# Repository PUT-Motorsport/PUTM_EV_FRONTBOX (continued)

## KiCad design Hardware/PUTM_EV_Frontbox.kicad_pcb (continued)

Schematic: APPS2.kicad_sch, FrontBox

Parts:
C50, C51, C52: 100n; C_0603_1608Metric_Pad1.08x0.95mm_HandSolder; Mouser Part Number .
C53: 10n; C_0603_1608Metric_Pad1.08x0.95mm_HandSolder; Mouser Part Number .; not fitted
R23, R27, R28, R29: 1K; R_0603_1608Metric_Pad0.98x0.95mm_HandSolder; Mouser Part Number .
R24: 100k; R_0603_1608Metric_Pad0.98x0.95mm_HandSolder; Mouser Part Number .
R25: 0R; R_0603_1608Metric_Pad0.98x0.95mm_HandSolder; Mouser Part Number .
R26: 325R; R_0603_1608Metric_Pad0.98x0.95mm_HandSolder; Mouser Part Number .
TP7: APPS_P; TestPoint_THTPad_D1.0mm_Drill0.5mm
TP8: APPS_OUT; TestPoint_THTPad_D1.0mm_Drill0.5mm
TP9: APPS_N; TestPoint_THTPad_D1.0mm_Drill0.5mm
U10: MCP6N11-001E/SN; SOIC-8_3.9x4.9mm_P1.27mm; Mouser Part Number 579-MCP6N11-001E/SN

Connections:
/APPS2_SHIFTED_3V3: R23.1; also elsewhere on the board
/APPS2_SHIFTED_GND: R26.2; also elsewhere on the board
/APPS2_SUPPLY: C50.1, C51.1, R23.2, R25.2, U10.7 (V+); also elsewhere on the board
/APPS_POT_2: R24.1, TP7.1, U10.3 (+); also elsewhere on the board
/APPS_SIG2: C52.1, R27.2, TP8.1; also elsewhere on the board
/DAC2_REF: C53.1, TP9.1, U10.2 (-); also elsewhere on the board
GND: C50.2, C51.2, C52.2, C53.2, R24.2, R26.1, R29.1, U10.4 (V-), U10.5 (RF); also elsewhere on the board
unnamed: R27.1, R28.2, U10.6
unnamed: R25.1, U10.8 (EN)
unnamed: R28.1, R29.2, U10.1 (FG)

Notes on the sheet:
3V3_POT2
Instrumentation Amplifier
Currently 1,566V - should be smaller than POT voltage
G = 2
f_{c} ≈ 1591
GND
Low-pass Filter
7K5
325R

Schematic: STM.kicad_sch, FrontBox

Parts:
C19: 10u; C_0805_2012Metric_Pad1.18x1.45mm_HandSolder; Mouser Part Number .
C20, C21, C22, C23, C24, C25, C26: 100nF; C_0603_1608Metric_Pad1.08x0.95mm_HandSolder; Mouser Part Number .
C27: 100n; C_0603_1608Metric; Mouser Part Number .
D11, D12, D13, D14: LED; LED_0603_1608Metric_Pad1.05x0.95mm_HandSolder; Mouser Part Number .
FB10: 2K@100MHz; L_0805_2012Metric_Pad1.05x1.20mm_HandSolder; Mouser Part Number 623-2508052027Y1
JP2: Jumper_2_Small_Bridged; SolderJumper-2_P1.3mm_Open_TrianglePad1.0x1.5mm; Mouser Part Number .
R6: 1k; R_0603_1608Metric; Mouser Part Number .
R7, R9: 10k; R_0603_1608Metric; Mouser Part Number .
R8: 10k; R_0603_1608Metric; Mouser Part Number .; not fitted
R10, R11, R12, R13: 1K; R_0603_1608Metric_Pad0.98x0.95mm_HandSolder; Mouser Part Number .
TP3: TestPoint_Small; TestPoint_THTPad_D1.0mm_Drill0.5mm
U5: LM4040C33FTA; SOT-23; Mouser Part Number 621-LM4040C33FTA
U6: STM32G484RETx; LQFP-64_10x10mm_P0.5mm; Mouser Part Number .

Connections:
+3.3V: C19.1, C20.1, C21.1, C22.1, C23.1, C24.1, D11.2 (A), D12.2 (A), D13.2 (A), D14.2 (A), FB10.1, R7.1, R8.1, U6.1 (VBAT), U6.16 (VDD), U6.32 (VDD), U6.48 (VDD), U6.64 (VDD); also elsewhere on the board
+3.3VA: C25.1, FB10.2, U6.29 (VDDA); also elsewhere on the board
+5V: R6.1; also elsewhere on the board
/APPS_SIG1: U6.18 (ADC2_IN17); also elsewhere on the board
/APPS_SIG2: U6.17 (ADC1_IN4); also elsewhere on the board
/BRAKE_PRESSURE_FRONT_OUT: U6.22 (ADC2_IN5); also elsewhere on the board
/BRAKE_PRESSURE_REAR_OUT: U6.21 (ADC2_IN4); also elsewhere on the board
/CAN bus/CAN1_RX: U6.45 (FDCAN1_RX); also elsewhere on the board
/CAN bus/CAN1_TX: U6.46 (FDCAN1_TX); also elsewhere on the board
/CAN bus/CAN2_RX: U6.34 (FDCAN2_RX); also elsewhere on the board
/CAN bus/CAN2_TX: U6.35 (FDCAN2_TX); also elsewhere on the board
/CAN bus/STBY_CAN_1: U6.3 (PC14); also elsewhere on the board
/CAN bus/STBY_CAN_2: U6.4 (PC15); also elsewhere on the board
/Connector/NRST: C27.1, JP2.2 (B), R7.2, U6.7 (PG10); also elsewhere on the board
/Connector/SWCLK: U6.50 (SYS_JTCK-SWCLK); also elsewhere on the board
/Connector/SWDIO: U6.49 (SYS_JTMS-SWDIO); also elsewhere on the board
/Connector/SWO: U6.56 (SYS_JTDO-SWO); also elsewhere on the board
/Connector/UART_RX: U6.44 (USART1_RX); also elsewhere on the board
/Connector/UART_RX_PROG: U6.30 (LPUART1_RX); also elsewhere on the board
/Connector/UART_TX: U6.43 (USART1_TX); also elsewhere on the board
/Connector/UART_TX_PROG: U6.9 (LPUART1_TX); also elsewhere on the board
/DAC1_REF: U6.20 (DAC2_OUT1); also elsewhere on the board
/DAC2_REF: U6.19 (DAC1_OUT2); also elsewhere on the board
/HSE_IN: U6.5 (RCC_OSC_IN); also elsewhere on the board
/MCU/BOOT: R8.2, R9.1, U6.61 (PB8)
/MCU/BSPD_S: U6.62 (PB9); also elsewhere on the board
/MCU/DEBUG_LED1: R10.2, U6.39 (PC7)
/MCU/DEBUG_LED2: R11.2, U6.38 (PC6)
/MCU/DEBUG_LED3: R12.2, U6.37 (PB15)
/MCU/DEBUG_LED4: R13.2, U6.36 (PB14)
/MCU/DRIVER_KILL_S: U6.54 (PC12); also elsewhere on the board
/MCU/EBS_S: U6.52 (PC10); also elsewhere on the board
/MCU/INERTIA_S: U6.51 (PA15); also elsewhere on the board
/MCU/LEFT_KILL_S: U6.53 (PC11); also elsewhere on the board
/MCU/LEFT_WHEEL_S: U6.57 (PB4); also elsewhere on the board
/MCU/OVERTRAVEL_S: U6.59 (PB6); also elsewhere on the board
/MCU/RIGHT_KILL_S: U6.60 (PB7); also elsewhere on the board
/MCU/RIGHT_WHEEL_S: U6.58 (PB5); also elsewhere on the board
/MCU/Tens1: U6.12 (ADC1_IN1); also elsewhere on the board
/MCU/Tens2: U6.13 (ADC1_IN2); also elsewhere on the board
/MCU/VREF: C26.1, R6.2, TP3.1, U5.1 (K), U6.28 (VREF+)
/MCU/XIAO_GPIO: U6.42 (PA8); also elsewhere on the board
GND: C19.2, C20.2, C21.2, C22.2, C23.2, C24.2, C25.2, C26.2, C27.2, JP2.1 (A), R9.2, U5.2 (A), U6.15 (VSS), U6.27 (VSSA), U6.31 (VSS), U6.47 (VSS), U6.63 (VSS); also elsewhere on the board
unnamed: D11.1 (K), R10.1
unnamed: D12.1 (K), R11.1
unnamed: D13.1 (K), R12.1
unnamed: D14.1 (K), R13.1

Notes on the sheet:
MCU
Decoupling capacitors
Debug LEDs

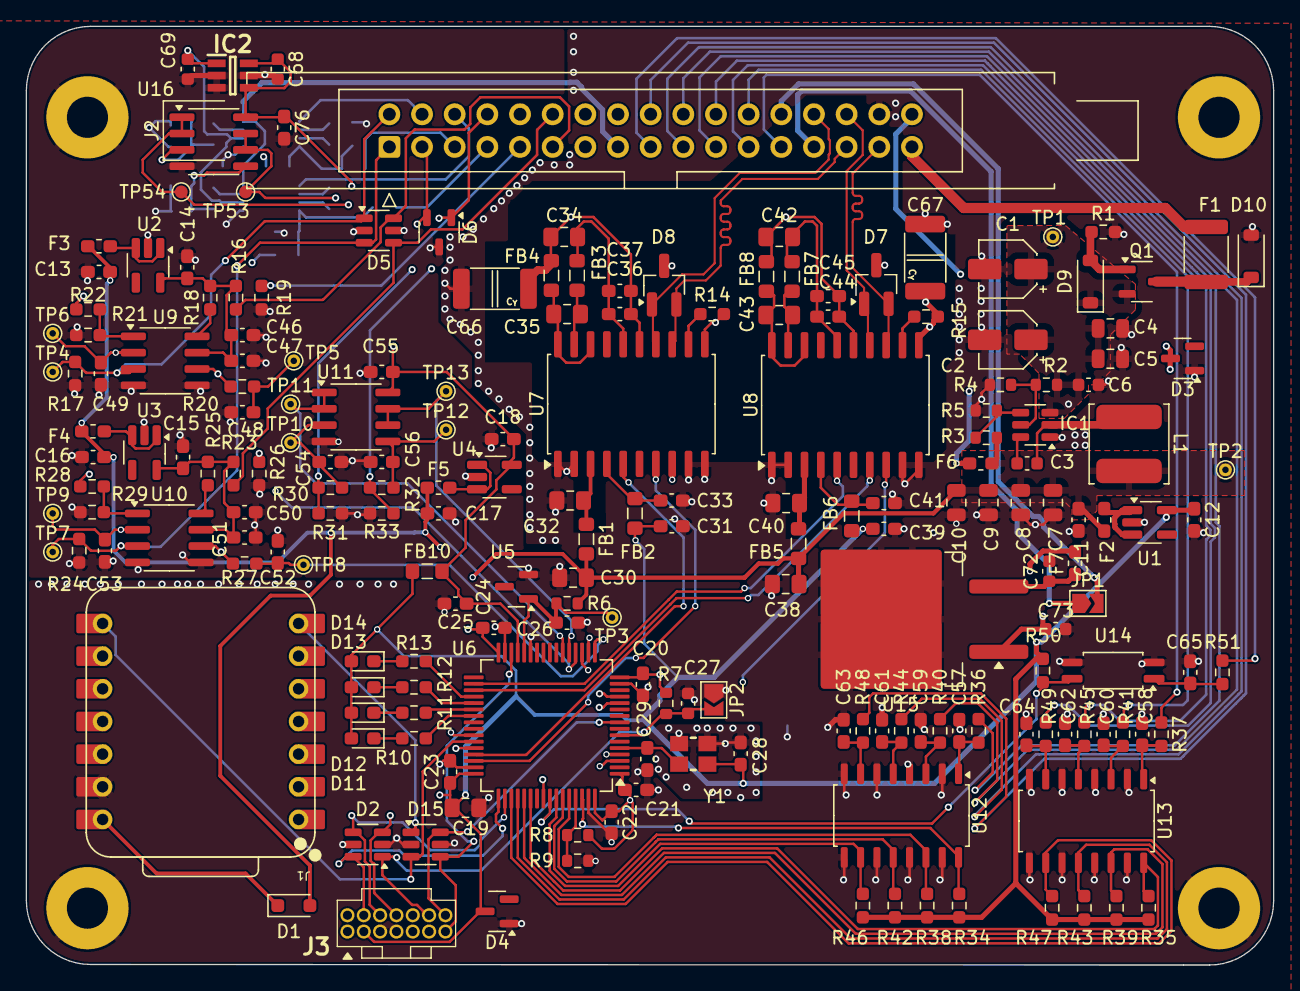
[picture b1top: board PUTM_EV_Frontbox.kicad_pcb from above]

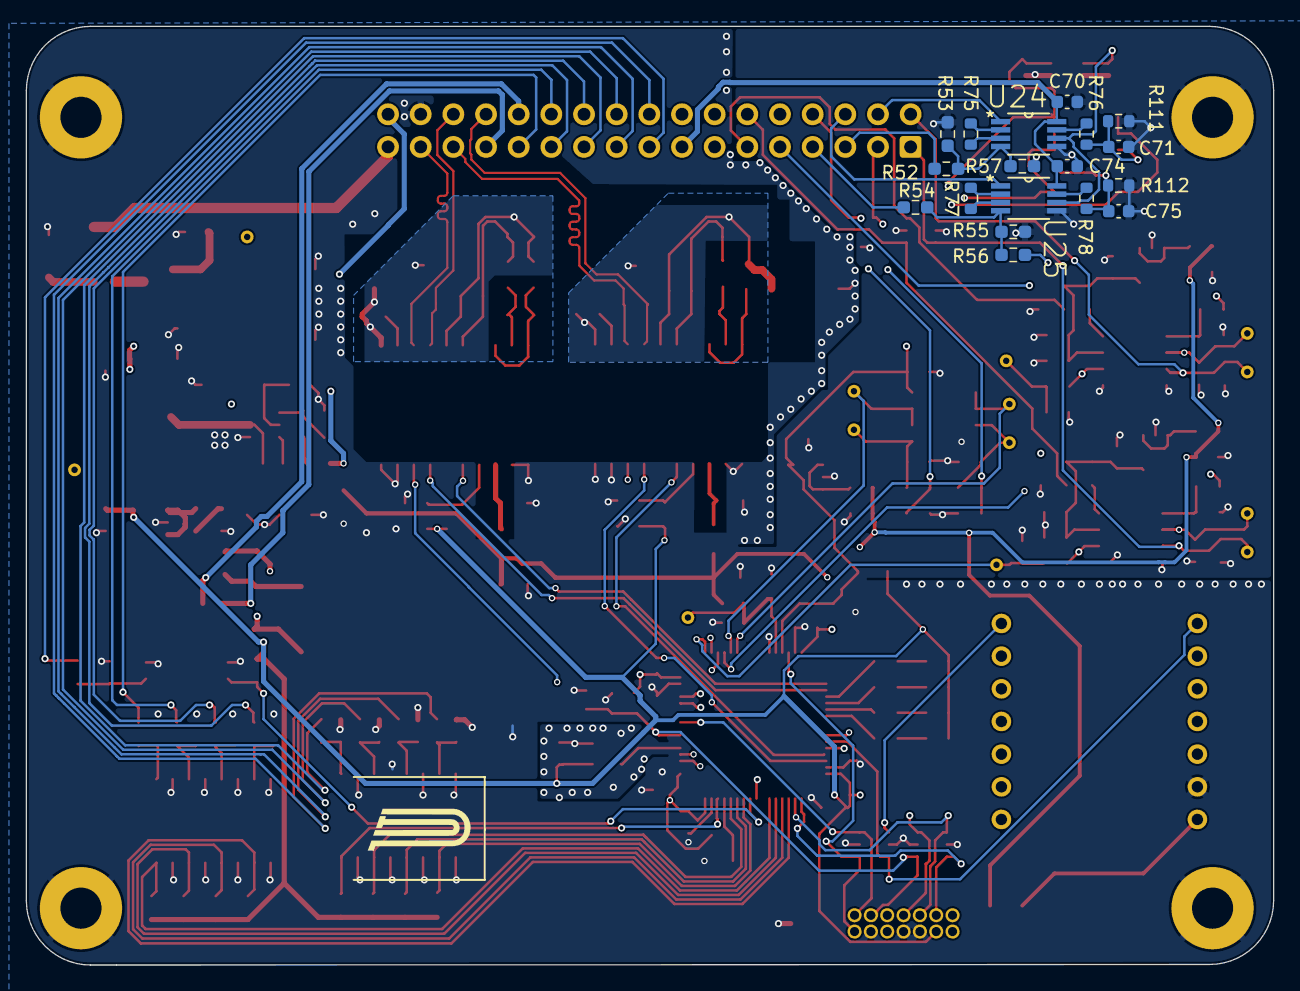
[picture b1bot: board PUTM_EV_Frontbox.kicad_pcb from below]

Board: 4 copper layers, 97.0 x 73.0 mm, 213 parts (18 on the bottom side), 134 nets.

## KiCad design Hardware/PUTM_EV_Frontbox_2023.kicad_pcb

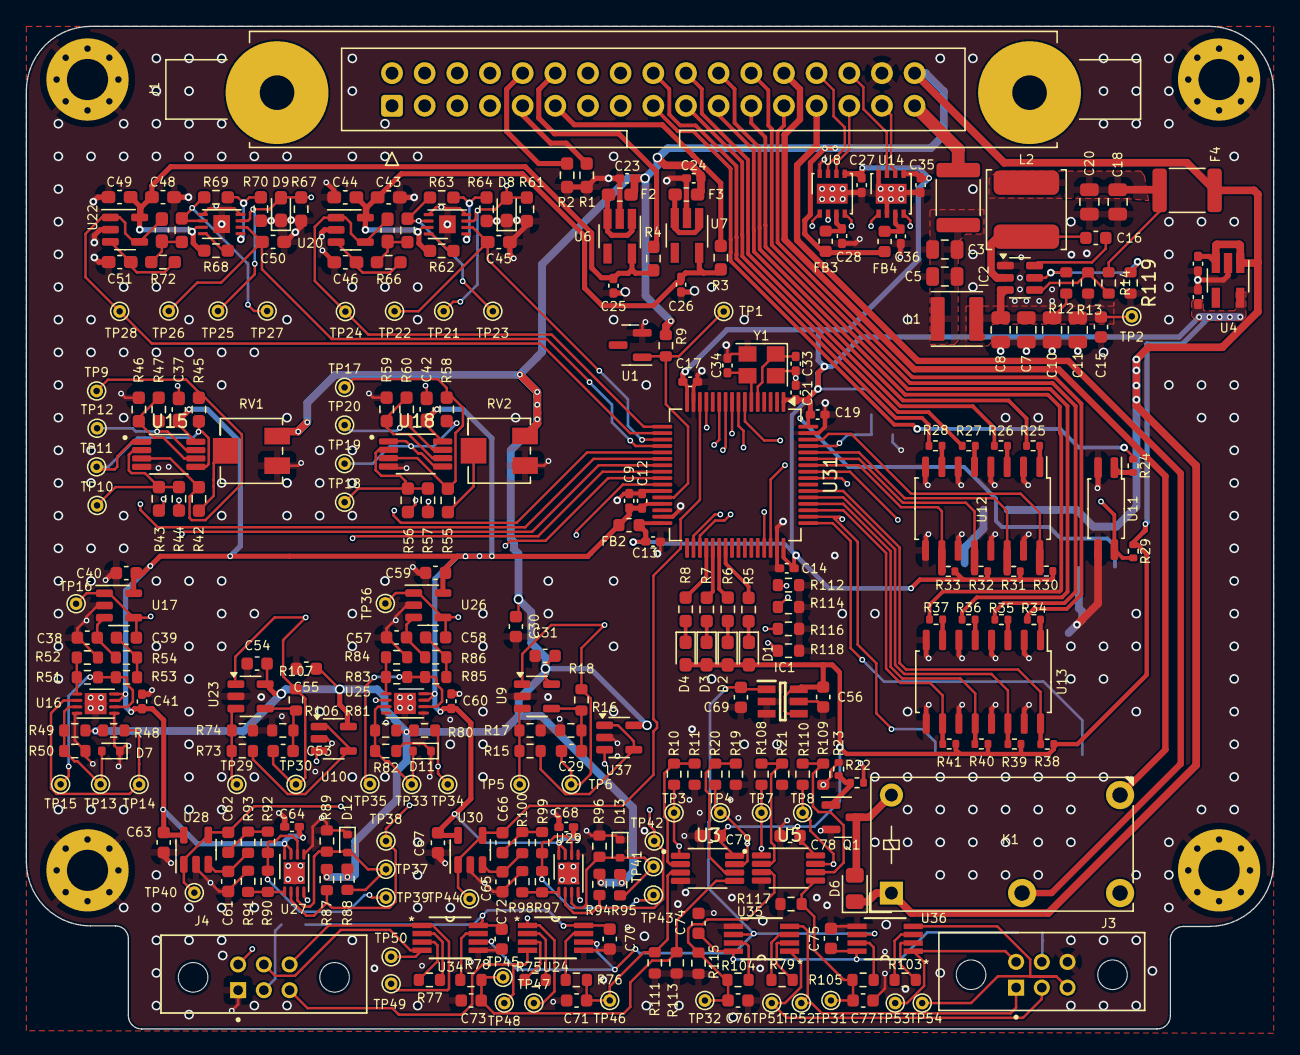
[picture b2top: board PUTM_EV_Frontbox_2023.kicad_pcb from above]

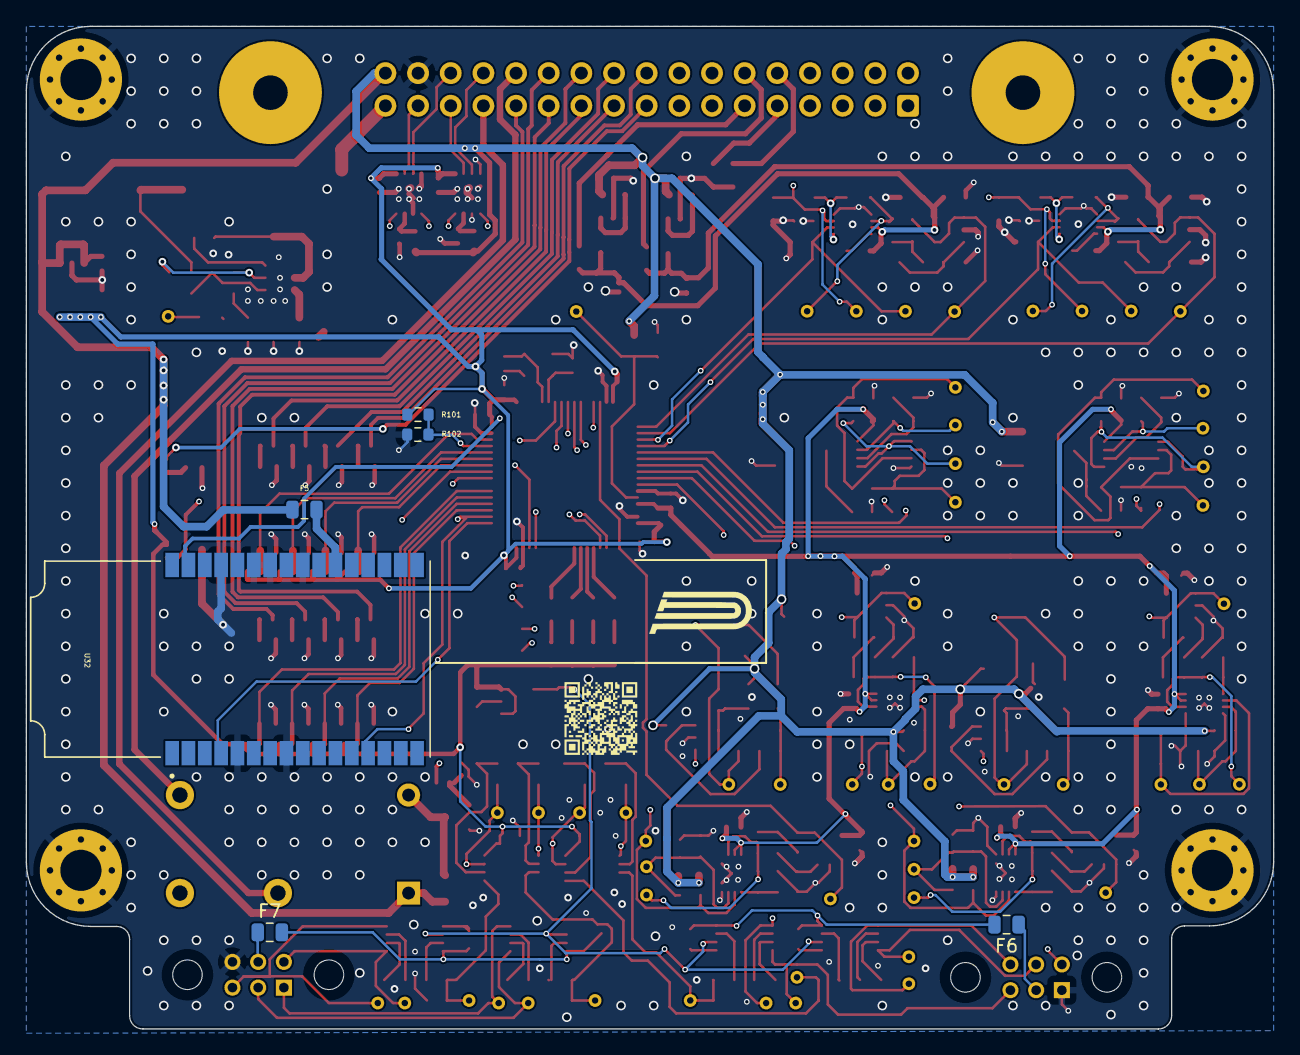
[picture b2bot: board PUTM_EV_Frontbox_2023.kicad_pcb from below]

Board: 4 copper layers, 97.0 x 78.0 mm, 320 parts (6 on the bottom side), 183 nets.

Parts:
C3, C5: 2u2; C_0805_2012Metric
C4, C6, C9, C23, C24, C25, C26: 1uF; C_0402_1005Metric_Pad0.74x0.62mm_HandSolder
C7, C8: 4u7; C_0805_2012Metric
C10, C11, C18, C20: 22uF; C_0805_2012Metric
C12, C13, C14, C17, C19, C21, C27, C28, C35, C36: 100nF; C_0402_1005Metric_Pad0.74x0.62mm_HandSolder
C15, C16: 100nF; C_0603_1608Metric
C29, C53: 10n; C_0603_1608Metric
C30, C31, C38, C39, C40, C54, C55, C57, C58, C59, C61, C62, C63, C65, C66, C67, C70, C72, C74, C75, C78, C79: 100n; C_0603_1608Metric
C33, C34: 10pF; C_0402_1005Metric_Pad0.74x0.62mm_HandSolder
C37, C42, C43, C44, C46, C47, C48, C49, C51, C52: 100n; C_0603_1608Metric_Pad1.08x0.95mm_HandSolder
C41, C60, C64, C68: 100n; C_0402_1005Metric_Pad0.74x0.62mm_HandSolder
C45, C50: 10n; C_0603_1608Metric_Pad1.08x0.95mm_HandSolder
C56, C71, C73, C76, C77: 1u; C_0603_1608Metric
C69: 1n; C_0603_1608Metric
D1, D2, D3, D4: LED; LED_0603_1608Metric_Pad1.05x0.95mm_HandSolder
D6: D_Small; D_0805_2012Metric_Pad1.15x1.40mm_HandSolder
D7, D11, D12, D13: 5V; D_SOD-523
D8, D9: 24V; D_0603_1608Metric_Pad1.05x0.95mm_HandSolder
F1, F4: 1.5A; Fuse_1812_4532Metric
F2, F3: 300mA; Fuse_0603_1608Metric_Pad1.05x0.95mm_HandSolder
F5: Fuse_Small; Fuse_0805_2012Metric
F6, F7: 0.5A; Fuse_0805_2012Metric
FB2: 1000Ω@100MHz; L_0603_1608Metric
FB3, FB4: 60R@100MHz; L_0603_1608Metric
H1, H2, H3, H4: MountingHole_Pad; MountingHole_3.2mm_M3_Pad_Via
IC1: MCP1501T-18E_CHY; SOT95P270X145-6N
IC2: TPS54202HDDCR; SOT-23-6
J1: Conn_02x16_Counter_Clockwise; IDC-Header_2x17-1MP_P2.54mm_Latch6.5mm_Vertical
J3, J4: M80-5100622; M80-5100622_HARWIN_M80-5100622
K1: FINDER-32.21-x000; Relay_SPDT_Finder_32.21-x000
L1: 1u5; L_Abracon_ASPI-4030S
L2: 68uH/1.4A; L_TDK_VLS6045EX_VLS6045AF
Q1: NX7002AK; SOT-23
R1, R2, R3, R4: 220R; R_0603_1608Metric_Pad0.98x0.95mm_HandSolder
R5, R6, R7, R8, R42, R44, R55, R57: 100R; R_0603_1608Metric_Pad0.98x0.95mm_HandSolder
R9, R75, R77, R79, R103: 1k; R_0603_1608Metric
R10, R11, R19, R20, R21, R108, R109, R110: 0R; R_0603_1608Metric
R12: 510k; R_0603_1608Metric
R13: 13.3k; R_0603_1608Metric
R14: 100k; R_0603_1608Metric
R15, R16, R73, R106: 20k; R_0603_1608Metric
R17, R18, R74, R101, R102, R107: 10k; R_0603_1608Metric
R22: 200R; R_0402_1005Metric
R23, R29, R30, R31, R32, R33, R38, R39, R40, R41: 10k; R_0402_1005Metric
R24, R25, R26, R27, R28, R34, R35, R36, R37: 2k; R_0402_1005Metric
R43, R45, R47, R56, R58, R60, R62, R68: 0R; R_0603_1608Metric_Pad0.98x0.95mm_HandSolder
R46, R59: 3k3; R_0603_1608Metric_Pad0.98x0.95mm_HandSolder
R48, R49, R80, R81, R87, R88, R94, R95: 50k; R_0603_1608Metric
R50, R82, R89, R96: 5k; R_0603_1608Metric
R51, R52, R83, R84, R90, R91, R97, R98: TBD; R_0603_1608Metric
R53, R54, R85, R86, R92, R93, R99, R100: 3k3; R_0603_1608Metric
R61, R67: 100k; R_0603_1608Metric_Pad0.98x0.95mm_HandSolder
R63, R65, R66, R69, R71, R72: 4k7; R_0603_1608Metric_Pad0.98x0.95mm_HandSolder
R64, R70: 1k; R_0603_1608Metric_Pad0.98x0.95mm_HandSolder
R76, R78, R104, R105: 330; R_0603_1608Metric
R111, R112, R113, R114, R115, R116, R117, R118: 100K; R_0603_1608Metric
R119: 43k; R_0603_1608Metric
RV1, RV2: 2k; Potentiometer_Bourns_3214J_Horizontal
TP1, TP2, TP5, TP6, TP13, TP14, TP15, TP16, TP29, TP30, TP33, TP34, TP35, TP36, TP37, TP38, TP39, TP40, TP41, TP42, TP43, TP44: TestPoint_Small; TestPoint_THTPad_D1.0mm_Drill0.5mm
TP3, TP4, TP7, TP8, TP9, TP17, TP31, TP32, TP45, TP46, TP47, TP48, TP49, TP50, TP51, TP52, TP53, TP54: BR_N; TestPoint_THTPad_D1.0mm_Drill0.5mm
TP10, TP18: BR_P; TestPoint_THTPad_D1.0mm_Drill0.5mm
TP11, TP19: BR_MID; TestPoint_THTPad_D1.0mm_Drill0.5mm
TP12, TP20: BR_OUT; TestPoint_THTPad_D1.0mm_Drill0.5mm
TP21, TP25: APPS_P; TestPoint_THTPad_D1.0mm_Drill0.5mm
TP22, TP26: APPS_N; TestPoint_THTPad_D1.0mm_Drill0.5mm
TP23, TP27: APPS_MID; TestPoint_THTPad_D1.0mm_Drill0.5mm
TP24, TP28: APPS_OUT; TestPoint_THTPad_D1.0mm_Drill0.5mm
U1: LM4040C33FTA; SOT-23
U3, U5, U15, U18: MCP6002-xMS; SOP65P490X110-8N
U4, U6, U7: TLV743P; SOT-23-5_HandSoldering
U8, U14: MCP2542FDxMF; DFN-8-1EP_3x3mm_P0.65mm_EP1.55x2.4mm
U9, U10, U23, U37: MCP6001-OT; SOT-23-5
U11: FODM217B; SOP-4_4.4x2.6mm_P1.27mm
U12, U13: TLP291-4; SOIC-16_4.55x10.3mm_P1.27mm
U16, U25, U27, U29: MCP6N11-005; TDFN-8-1EP_3x2mm_P0.5mm_EP1.70x1.65mm
U17, U20, U22, U26, U28, U30: MCP6001; SOT-23-5
U19, U21: MCP6N11-005; TDFN-8-1EP_3x2mm_P0.5mm_EP1.3x1.4mm
U24, U34, U35, U36: AD8226BRMZ-R7; AD8226BRMZ-R7_SOP65P490X110-8N
U31: STM32G484RETx; LQFP-64_10x10mm_P0.5mm
U32: STLINK-V3MODS; MODULE_STLINK-V3MODS
Y1: ABM8G-48.000MHZ; Crystal_SMD_Abracon_ABM8G-4Pin_3.2x2.5mm

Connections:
+3.3V: C6.1, C13.1, C14.1, C17.1, C19.1, C21.1, C27.1, C35.1, C56.1, C78.1, C79.1, D1.2 (A), D2.2 (A), D3.2 (A), D4.2 (A), FB2.1, IC1.4 (~SHDN), IC1.6 (VDD), R29.1, R30.1, R31.1, R32.1, R33.1, R38.1, R39.1, R40.1, R41.1, R101.1, U3.8 (V+), U4.5 (OUT), U5.8 (V+), U8.5 (VIO), U14.5 (VIO), U31.1 (VBAT), U31.16 (VDD), U31.32 (VDD), U31.48 (VDD), U31.64 (VDD)
+3.3VA: C9.1, C12.1, C37.1, C40.1, C41.1, C42.1, C59.1, C60.1, C63.1, C64.1, C67.1, C68.1, FB2.2, U15.8 (V+), U16.7 (V+), U16.8 (EN), U17.5 (V+), U18.8 (V+), U25.7 (V+), U25.8 (EN), U26.5 (V+), U27.7 (V+), U27.8 (EN), U28.5 (V+), U29.7 (V+), U29.8 (EN), U30.5 (V+), U31.29 (VDDA)
+5V: C4.1, C23.1, C24.1, C30.1, C31.1, C54.1, C55.1, D6.1 (K), F2.1, F3.1, F4.2, F5.1, FB3.1, FB4.1, J1.34, K1.A1, R9.1, R48.1, R49.1, R80.1, R81.1, R87.1, R88.1, R94.1, R95.1, RV1.1, RV2.1, U4.1 (IN), U4.3 (EN), U9.5 (V+), U10.5 (V+), U23.5 (V+), U37.5 (V+)
+12V_LEFT: C70.1, C72.1, F6.2, U24.8 (+VS), U34.8 (+VS)
+12V_RIGHT: C74.1, C75.1, F7.2, U35.8 (+VS), U36.8 (+VS)
+24V: F1.1, J1.33
/APPS1_3V3: C25.1, C48.1, C49.1, R4.1, R68.2, U6.5 (OUT), U21.7 (V+), U22.5 (V+)
/APPS1_SHIFTED_3V3: J1.11, R3.2
/APPS1_SHIFTED_GND: J1.9, R1.2
/APPS2_3V3: C26.1, C43.1, C44.1, R3.1, R62.2, U7.5 (OUT), U19.7 (V+), U20.5 (V+)
/APPS2_SHIFTED_3V3: J1.12, R4.2
/APPS2_SHIFTED_GND: J1.10, R2.2
/APPS_POT_1: D9.2 (A2), J1.2, R67.1, TP25.1, U21.3 (+)
/APPS_POT_2: D8.2 (A2), J1.1, R61.1, TP21.1, U19.3 (+)
/APPS_sig1: C52.2, TP28.1, U22.1, U22.4 (-), U31.18 (PA4)
/APPS_sig2: C47.2, TP24.1, U20.1, U20.4 (-), U31.17 (PA3)
/BRAKE_PRESSURE1_IN: J1.3, R43.2
/BRAKE_PRESSURE2_IN: J1.8, R56.2
/BRAKE_PRESSURE_FRONT_OUT: R47.1, TP12.1, U15.7, U31.22 (PC4)
/BRAKE_PRESSURE_REAR_OUT: R60.1, TP20.1, U18.7, U31.21 (PA7)
/BSPD_SENSE: J1.21, R25.1
/CAN1+: J1.28, U8.7 (CANH)
/CAN1-: J1.29, U8.6 (CANL)
/CAN1_RX: U8.4 (RXD), U31.45 (PA11)
/CAN1_TX: U8.1 (TXD), U31.46 (PA12)
/CAN2+: J1.30, U14.7 (CANH)
/CAN2-: J1.31, U14.6 (CANL)
/CAN2_RX: U14.4 (RXD), U31.34 (PB12)
/CAN2_TX: U14.1 (TXD), U31.35 (PB13)
/DAC1_REF: C50.1, TP26.1, U21.2 (-), U31.20 (PA6)
/DAC2_REF: C45.1, TP22.1, U19.2 (-), U31.19 (PA5)
/DEBUG_LED1: R5.2, U31.39 (PC7)
/DEBUG_LED2: R6.2, U31.38 (PC6)
/DEBUG_LED3: R7.2, U31.37 (PB15)
/DEBUG_LED4: R8.2, U31.36 (PB14)
/EBS_SAFETY: J1.23, R36.1
/GEARBOX_TEMP_1: C62.2, TP40.1, U28.1, U28.4 (-), U31.13 (PA1)
/GEARBOX_TEMP_2: C66.2, TP44.1, U30.1, U30.4 (-), U31.14 (PA2)
/Gearbox_Temp_sensor_1/IN+: D12.2 (A2), R88.2, R89.1, TP37.1, U27.3 (+)
/Gearbox_Temp_sensor_2/IN+: D13.2 (A2), R95.2, R96.1, TP41.1, U29.3 (+)
/HSE_IN: C33.1, U31.5 (PF0), Y1.1
/HSE_OUT: C34.1, U31.6 (PF1), Y1.3
/INERTIA: J1.22, R37.1
/KILL_KIERA: J1.25, R34.1
/KILL_LEWY: J1.24, R35.1
/KILL_PRAWY: J1.20, R26.1
/LEFT_WHEEL_SC: J1.17, R24.1
/NRST: U31.7 (PG10), U32.31 (T_NRST)
/OVERTRAVEL: J1.19, R27.1
/PT100_1: J1.14, R87.2, TP38.1, U27.2 (-)
/PT100_2: J1.13, R94.2, TP42.1, U29.2 (-)
/Power section/5V_UNFUSED: C18.1, C20.1, F4.1, L2.2, R14.2
/Power section/+24V_FUSED: C3.1, C5.1, F1.2, L1.1
/Power section/BOOT_5V: C16.1, IC2.6 (BOOT)
/Power section/EN_5V: IC2.5 (EN), R12.1, R119.1
/Power section/FB_5V: IC2.4 (FB), R13.2, R14.1
/Power section/SW_5V: C16.2, IC2.2 (SW), L2.1
/RIGHT_WHEEL_SC: J1.18, R28.1
/SAFE-IN: J1.27, K1.11
/SAFE-OUT: J1.26, K1.12
/STEERING_POSITION_2_IN: J1.7, U37.3 (+)
/STEERING_POSITION_2_OUT: C29.1, R18.2, TP6.1, U9.1, U31.26 (PB2)
/STEERING_POSITION_IN: J1.5, U10.3 (+)
/STEERING_POSITION_OUT: C53.1, R107.2, TP30.1, U23.1, U31.24 (PB0)
/SUSPENSION_POT1_IN: J1.4, R48.2, TP14.1, U16.2 (-)
/SUSPENSION_POT2_IN: J1.6, R80.2, TP34.1, U25.2 (-)
/SUSP_L_OUT: C39.2, TP16.1, U17.1, U17.4 (-), U31.23 (PC5)
/SUSP_R_OUT: C58.2, TP36.1, U26.1, U26.4 (-), U31.25 (PB1)
/SWCLK: U31.50 (PA14), U32.13 (T_JCLK/T_SWCLK)
/SWDIO: U31.49 (PA13), U32.4 (T_JTMS/T_SWDIO)
/Safety sense/SLW_A: R24.2, U11.1
/Safety_control: R22.1, U31.56 (PB3)
/Sense_BSPD: R30.2, U12.16, U31.62 (PB9)
/Sense_EBS: R40.2, U13.12, U31.52 (PC10)
/Sense_Left_Wheel: R29.2, U11.4, U31.57 (PB4)
/Sense_Right_Wheel: R33.2, U12.10, U31.58 (PB5)
/Sense_driver: R38.2, U13.16, U31.54 (PC12)
/Sense_inertia: R41.2, U13.10, U31.51 (PA15)
/Sense_left: R39.2, U13.14, U31.53 (PC11)
/Sense_overtravel: R32.2, U12.12, U31.59 (PB6)
/Sense_right: R31.2, U12.14, U31.60 (PB7)
/Suspension Potentiometer (Left)/IN+: D7.2 (A2), R49.2, R50.1, TP13.1, U16.3 (+)
/Suspension Potentiometer (Right)/IN+: D11.2 (A2), R81.2, R82.1, TP33.1, U25.3 (+)
/Tensometer 1: R10.1, R112.1, TP3.1, U3.1, U31.8 (PC0)
/Tensometer 2: R20.1, R114.1, TP4.1, U3.7, U31.9 (PC1)
/Tensometer 3: R108.1, R116.1, TP7.1, U5.1, U31.10 (PC2)
/Tensometer 4: R110.1, R118.1, TP8.1, U5.7, U31.11 (PC3)
/Tensometers/1,8V: C69.2, IC1.1 (OUT), U24.6 (REF), U34.6 (REF), U35.6 (REF), U36.6 (REF)
/Tensometers/12V1: F6.1, J4.2
/Tensometers/12V2: F7.1, J3.5
/Tensometers/OUT1+: J4.3, TP48.1, U24.4 (+IN)
/Tensometers/OUT1-: J4.4, TP47.1, U24.1 (-IN)
/Tensometers/OUT2+: J4.5, TP50.1, U34.4 (+IN)
/Tensometers/OUT2-: J4.6, TP49.1, U34.1 (-IN)
/Tensometers/OUT3+: J3.1, TP52.1, U35.4 (+IN)
/Tensometers/OUT3-: J3.2, TP51.1, U35.1 (-IN)
/Tensometers/OUT4+: J3.3, TP54.1, U36.4 (+IN)
/Tensometers/OUT4-: J3.4, TP53.1, U36.1 (-IN)
/VREF: R9.2, TP1.1, U1.1 (K), U31.28 (VREF+)
GND: C3.2, C4.2, C5.2, C6.2, C7.2, C8.2, C9.2, C10.1, C11.1, C12.2, C13.2, C14.2, C15.1, C17.2, C18.2, C19.2, C20.2, C21.2, C23.2, C24.2, C25.2, C26.2, C27.2, C28.2, C30.2, C31.2, C33.2, C34.2, C35.2, C36.2, C37.2, C38.2, C40.2, C41.2, C42.2, C43.2, C44.2, C45.2, C46.2, C48.2, C49.2, C50.2, C51.2, C54.2, C55.2, C56.2, C57.2, C59.2, C60.2, C61.2, C63.2, C64.2, C65.2, C67.2, C68.2, C69.1, C70.2, C71.2, C72.2, C73.2, C74.2, C75.2, C76.2, C77.2, C78.2, C79.2, D7.1 (A1), D8.1 (A1), D9.1 (A1), D11.1 (A1), D12.1 (A1), D13.1 (A1), H1.1, H2.1, H3.1, H4.1, IC1.2 (GND), IC1.3 (GND_2), IC1.5 (GND_3), IC2.1 (GND), J1.32, J3.6, J4.1, Q1.2 (S), R1.1, R2.1, R11.2, R13.1, R16.1, R17.2, R19.2, R21.2, R23.2, R44.1, R46.2, R50.2, R52.1, R57.1, R59.2, R61.2, R64.1, R67.2, R70.1, R74.2, R82.2, R84.1, R89.2, R91.1, R96.2, R98.1, R102.2, R106.1, R109.2, R111.2, R112.2, R113.2, R114.2, R115.2, R116.2, R117.2, R118.2, R119.2, RV1.3, RV2.3, U1.2 (A), U3.4 (V-), U4.2 (GND), U5.4 (V-), U6.2 (GND), U7.2 (GND), U8.2 (VSS), U8.8 (STBY), U8.9 (VSS), U9.2 (V-), U10.2 (V-), U11.2, U11.3, U12.2, U12.4, U12.6, U12.8, U12.9, U12.11, U12.13, U12.15, U13.2, U13.4, U13.6, U13.8, U13.9, U13.11, U13.13, U13.15, U14.2 (VSS), U14.8 (STBY), U14.9 (VSS), U15.4 (V-), U16.4 (V-), U16.5 (RF), U16.9 (EP), U17.2 (V-), U18.4 (V-), U19.4 (V-), U19.5 (RF), U19.9 (EP), U20.2 (V-), U21.4 (V-), U21.5 (RF), U21.9 (EP), U22.2 (V-), U23.2 (V-), U24.5 (-VS), U25.4 (V-), U25.5 (RF), U25.9 (EP), U26.2 (V-), U27.4 (V-), U27.5 (RF), U27.9 (EP), U28.2 (V-), U29.4 (V-), U29.5 (RF), U29.9 (EP), U30.2 (V-), U31.15 (VSS), U31.27 (VSSA), U31.31 (VSS), U31.47 (VSS), U31.63 (VSS), U32.5 (GNDDETECT), U32.8 (GND_2), U32.24 (GND), U32.26 (GND2), U32.27 (GND3), U32.29 (GND4), U34.5 (-VS), U35.5 (-VS), U36.5 (-VS), U37.2 (V-), Y1.2, Y1.4
unnamed: C39.1, R53.2, R54.1
unnamed: C47.1, R65.2, R66.1
unnamed: C52.1, R71.2, R72.1
unnamed: C58.1, R85.2, R86.1
unnamed: C62.1, R92.2, R93.1
unnamed: C66.1, R99.2, R100.1
unnamed: D1.1 (K), R5.1
unnamed: D2.1 (K), R6.1
unnamed: D3.1 (K), R7.1
unnamed: D4.1 (K), R8.1
unnamed: D6.2 (A), K1.A2, Q1.3 (D)
unnamed: C7.1, C8.1, C10.2, C11.2, C15.2, IC2.3 (VIN), L1.2, R12.2, TP2.1
unnamed: Q1.1 (G), R22.2, R23.1
unnamed: R25.2, U12.1
unnamed: R26.2, U12.3
unnamed: R27.2, U12.5
unnamed: R28.2, U12.7
unnamed: R34.2, U13.1
unnamed: R35.2, U13.3
unnamed: R36.2, U13.5
unnamed: R37.2, U13.7
unnamed: R42.2, RV1.2
unnamed: R51.2, R53.1, TP15.1, U16.6
unnamed: R55.2, RV2.2
unnamed: R63.2, R65.1, TP23.1, U19.6
unnamed: R69.2, R71.1, TP27.1, U21.6
unnamed: R83.2, R85.1, TP35.1, U25.6
unnamed: R90.2, R92.1, TP39.1, U27.6
unnamed: R97.2, R99.1, TP43.1, U29.6
unnamed: C71.1, R76.2, R111.1, TP46.1, U3.3 (+)
unnamed: R10.2, R11.1, U3.2 (-)
unnamed: C73.1, R78.2, R113.1, TP45.1, U3.5 (+)
unnamed: R19.1, R20.2, U3.6 (-)
unnamed: C76.1, R104.2, R115.1, TP32.1, U5.3 (+)
unnamed: R21.1, R108.2, U5.2 (-)
unnamed: C77.1, R105.2, R117.1, TP31.1, U5.5 (+)
unnamed: R109.1, R110.2, U5.6 (-)
unnamed: F2.2, U6.1 (IN), U6.3 (EN)
unnamed: F3.2, U7.1 (IN), U7.3 (EN)
unnamed: C28.1, FB3.2, U8.3 (VDD)
unnamed: R15.2, R17.1, TP5.1, U9.3 (+)
unnamed: C29.2, R16.2, R18.1, U9.4 (-)
unnamed: R73.1, U10.1, U10.4 (-)
unnamed: C36.1, FB4.2, U14.3 (VDD)
unnamed: R42.1, R45.2, TP9.1, U15.3 (+)
unnamed: R43.1, R44.2, TP10.1, U15.2 (-)
unnamed: R45.1, TP11.1, U15.1, U15.5 (+)
unnamed: R46.1, R47.2, U15.6 (-)
unnamed: R51.1, R52.2, U16.1 (FG)
unnamed: C38.1, R54.2, U17.3 (+)
unnamed: R55.1, R58.2, TP17.1, U18.3 (+)
unnamed: R56.1, R57.2, TP18.1, U18.2 (-)
unnamed: R58.1, TP19.1, U18.1, U18.5 (+)
unnamed: R59.1, R60.2, U18.6 (-)
unnamed: R62.1, U19.8 (EN)
unnamed: R63.1, R64.2, U19.1 (FG)
unnamed: C46.1, R66.2, U20.3 (+)
unnamed: R68.1, U21.8 (EN)
unnamed: R69.1, R70.2, U21.1 (FG)
unnamed: C51.1, R72.2, U22.3 (+)
unnamed: R73.2, R74.1, TP29.1, U23.3 (+)
unnamed: C53.2, R106.2, R107.1, U23.4 (-)
unnamed: R75.2, U24.3 (RG)
unnamed: R75.1, U24.2 (RG_2)
unnamed: R76.1, U24.7 (VOUT)
unnamed: R83.1, R84.2, U25.1 (FG)
unnamed: C57.1, R86.2, U26.3 (+)
unnamed: R90.1, R91.2, U27.1 (FG)
unnamed: C61.1, R93.2, U28.3 (+)
unnamed: R97.1, R98.2, U29.1 (FG)
unnamed: C65.1, R100.2, U30.3 (+)
unnamed: R101.2, R102.1, U31.61 (PB8)
unnamed: F5.2, U32.22 (5V_OPT)
unnamed: R77.2, U34.3 (RG)
unnamed: R77.1, U34.2 (RG_2)
unnamed: R78.1, U34.7 (VOUT)
unnamed: R79.2, U35.3 (RG)
unnamed: R79.1, U35.2 (RG_2)
unnamed: R104.1, U35.7 (VOUT)
unnamed: R103.2, U36.3 (RG)
unnamed: R103.1, U36.2 (RG_2)
unnamed: R105.1, U36.7 (VOUT)
unnamed: R15.1, U37.1, U37.4 (-)

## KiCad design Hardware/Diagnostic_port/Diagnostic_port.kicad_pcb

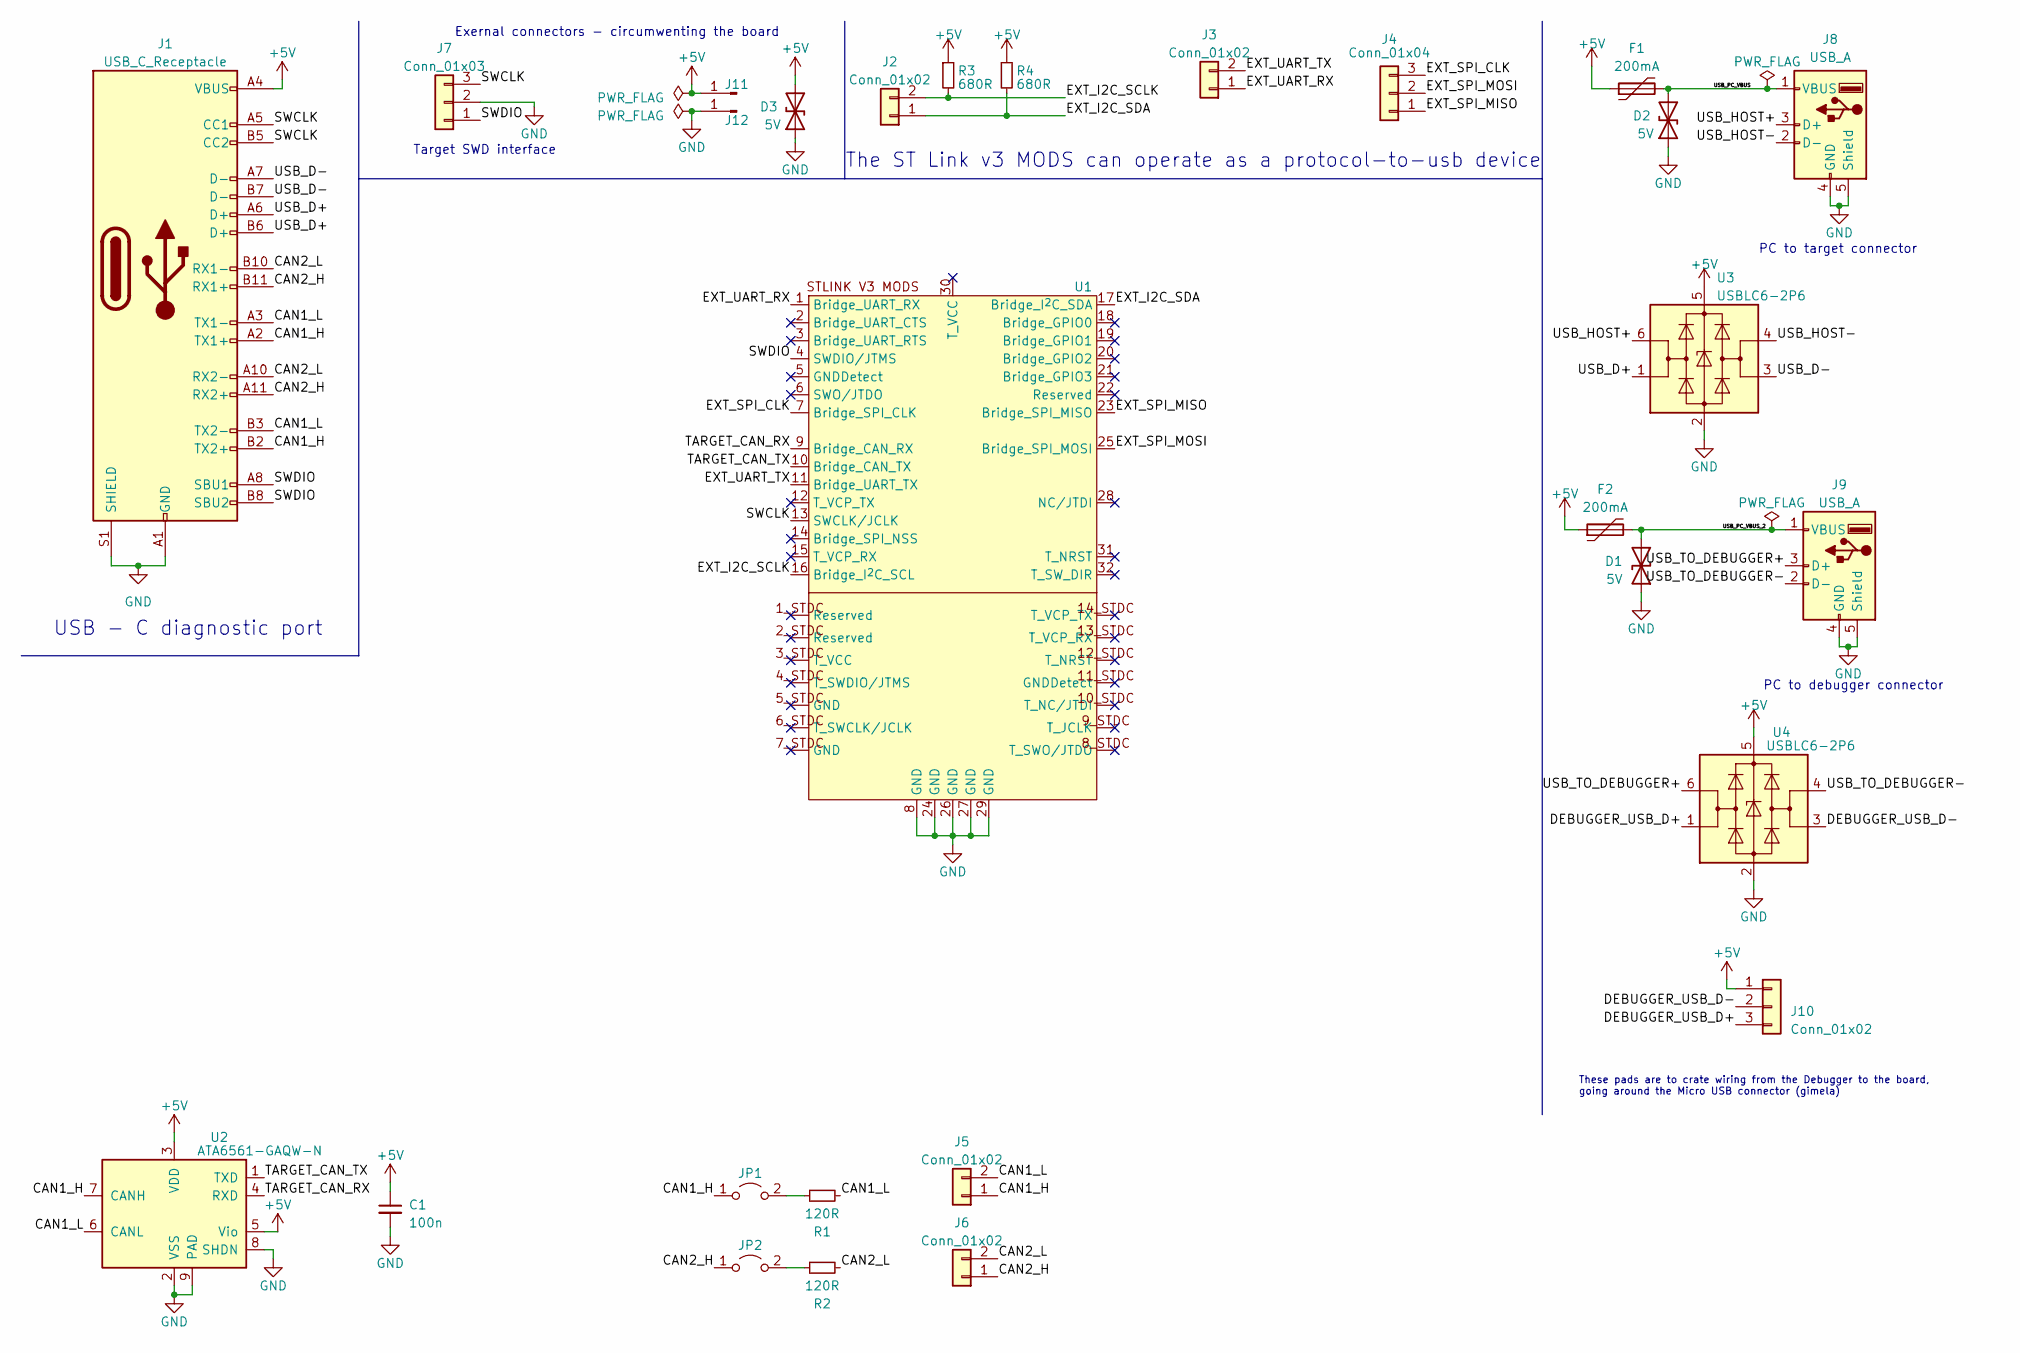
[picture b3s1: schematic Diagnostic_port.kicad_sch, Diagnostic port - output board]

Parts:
C1: 100n; C_0402_1005Metric_Pad0.74x0.62mm_HandSolder
D1, D2, D3: 5V; D_SOD-523
F1, F2: 200mA; Fuse_0603_1608Metric_Pad1.05x0.95mm_HandSolder
J1: USB_C_Receptacle; CUI_UJ31-CH-31-SMT-TR
J2, J3, J5, J6: Conn_01x02; PinHeader_1x02_P2.54mm_Vertical
J4: Conn_01x04; PinHeader_1x03_P2.54mm_Vertical
J7: Conn_01x03; PinHeader_1x03_P2.54mm_Vertical
J8, J9: USB_A; UP2-AH-TH
J10: Conn_01x02; PinSocket_1x03_P2.54mm_Vertical
J11, J12: Conn_01x01_Pin; SolderWirePad_1x01_SMD_5x10mm
JP1, JP2: Jumper_2_Open; PinHeader_1x02_P2.54mm_Vertical
R1, R2: 120R; R_0603_1608Metric_Pad0.98x0.95mm_HandSolder
R3, R4: 680R; R_0603_1608Metric_Pad0.98x0.95mm_HandSolder
U1: MODULE_STLINK-V3MODS
U2: ATA6561-GAQW-N; SOIC-8_3.9x4.9mm_P1.27mm
U3, U4: USBLC6-2P6; SOT-666

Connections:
+5V: C1.1, D3.2 (A2), F1.1, F2.1, J1.A4 (VBUS), J1.A9 (VBUS), J1.B4 (VBUS), J1.B9 (VBUS), J10.1, J11.1, R3.1, R4.1, U2.3 (VDD), U2.5 (Vio), U3.5 (VBUS), U4.5 (VBUS)
/CAN1_H: J1.A2 (TX1+), J1.B2 (TX2+), J5.1, JP1.1 (A), U2.7 (CANH)
/CAN1_L: J1.A3 (TX1-), J1.B3 (TX2-), J5.2, R1.2, U2.6 (CANL)
/CAN2_H: J1.A11 (RX2+), J1.B11 (RX1+), J6.1, JP2.1 (A)
/CAN2_L: J1.A10 (RX2-), J1.B10 (RX1-), J6.2, R2.2
/DEBUGGER_USB_D+: J10.3, U4.1 (I/O1)
/DEBUGGER_USB_D-: J10.2, U4.3 (I/O2)
/EXT_I2C_SCLK: J2.2, R3.2, U1.16 (Bridge_I^{2}C_SCL)
/EXT_I2C_SDA: J2.1, R4.2, U1.17 (Bridge_I^{2}C_SDA)
/EXT_SPI_CLK: J4.3, U1.7 (Bridge_SPI_CLK)
/EXT_SPI_MISO: J4.1, U1.23 (Bridge_SPI_MISO)
/EXT_SPI_MOSI: J4.2, U1.25 (Bridge_SPI_MOSI)
/EXT_UART_RX: J3.1, U1.1 (Bridge_UART_RX)
/EXT_UART_TX: J3.2, U1.11 (Bridge_UART_TX)
/SWCLK: J1.A5 (CC1), J1.B5 (CC2), J7.3, U1.13 (SWCLK/JCLK)
/SWDIO: J1.A8 (SBU1), J1.B8 (SBU2), J7.1, U1.4 (SWDIO/JTMS)
/TARGET_CAN_RX: U1.9 (Bridge_CAN_RX), U2.4 (RXD)
/TARGET_CAN_TX: U1.10 (Bridge_CAN_TX), U2.1 (TXD)
/USB_D+: J1.A6 (D+), J1.B6 (D+), U3.1 (I/O1)
/USB_D-: J1.A7 (D-), J1.B7 (D-), U3.3 (I/O2)
/USB_HOST+: J8.3 (D+), U3.6 (I/O1)
/USB_HOST-: J8.2 (D-), U3.4 (I/O2)
/USB_PC_VBUS: D2.2 (A2), F1.2, J8.1 (VBUS)
/USB_PC_VBUS_2: D1.2 (A2), F2.2, J9.1 (VBUS)
/USB_TO_DEBUGGER+: J9.3 (D+), U4.6 (I/O1)
/USB_TO_DEBUGGER-: J9.2 (D-), U4.4 (I/O2)
GND: C1.2, D1.1 (A1), D2.1 (A1), D3.1 (A1), J1.A1 (GND), J1.A12 (GND), J1.B1 (GND), J1.B12 (GND), J1.S1 (SHIELD), J7.2, J8.4 (GND), J8.5 (Shield), J9.4 (GND), J9.5 (Shield), J12.1, U1.8 (GND), U1.24 (GND), U1.26 (GND), U1.27 (GND), U1.29 (GND), U2.2 (VSS), U2.8 (SHDN), U2.9 (PAD), U3.2 (GND), U4.2 (GND)
unnamed: JP1.2 (B), R1.1
unnamed: JP2.2 (B), R2.1

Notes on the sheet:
USB - C diagnostic port
The ST Link v3 MODS can operate as a protocol-to-usb device
These pads are to crate wiring from the Debugger to the board, going around the Micro USB connector (gimela)
Exernal connectors - circumwenting the board
Target SWD interface
PC to target connector
PC to debugger connector

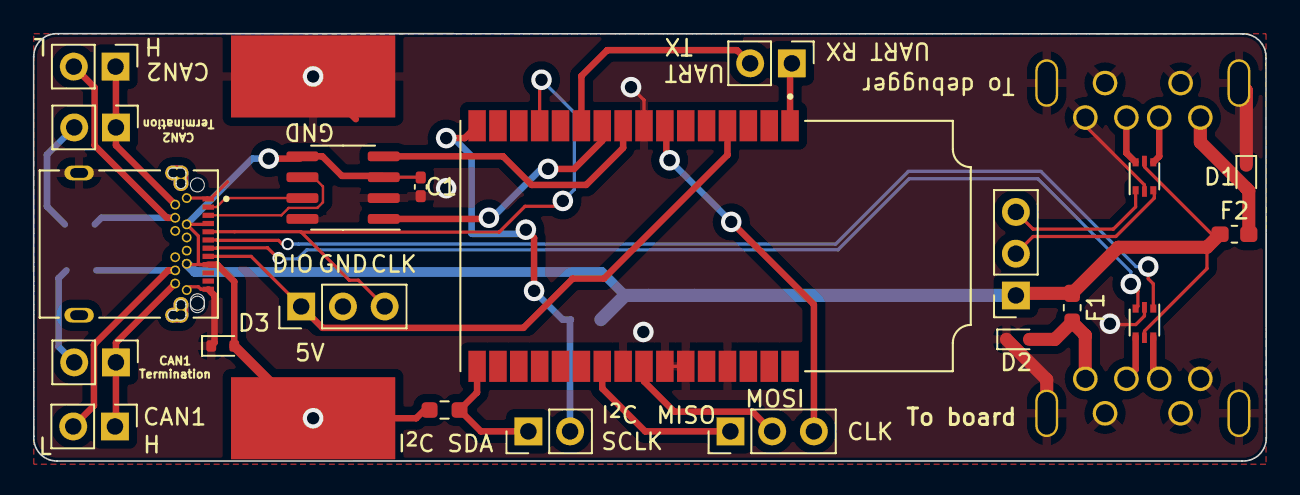
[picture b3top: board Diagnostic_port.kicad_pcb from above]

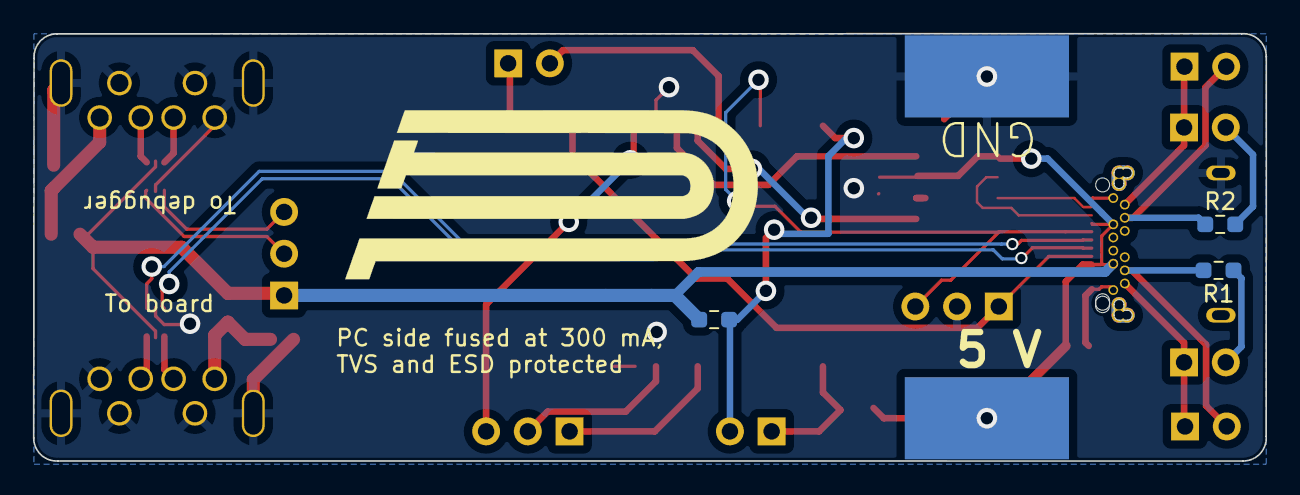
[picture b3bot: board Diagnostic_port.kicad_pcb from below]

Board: 2 copper layers, 75.0 x 26.0 mm, 29 parts (4 on the bottom side), 29 nets.

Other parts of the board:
J11#2: Conn_01x01_Pin; SolderWirePad_1x01_SMD_5x10mm
